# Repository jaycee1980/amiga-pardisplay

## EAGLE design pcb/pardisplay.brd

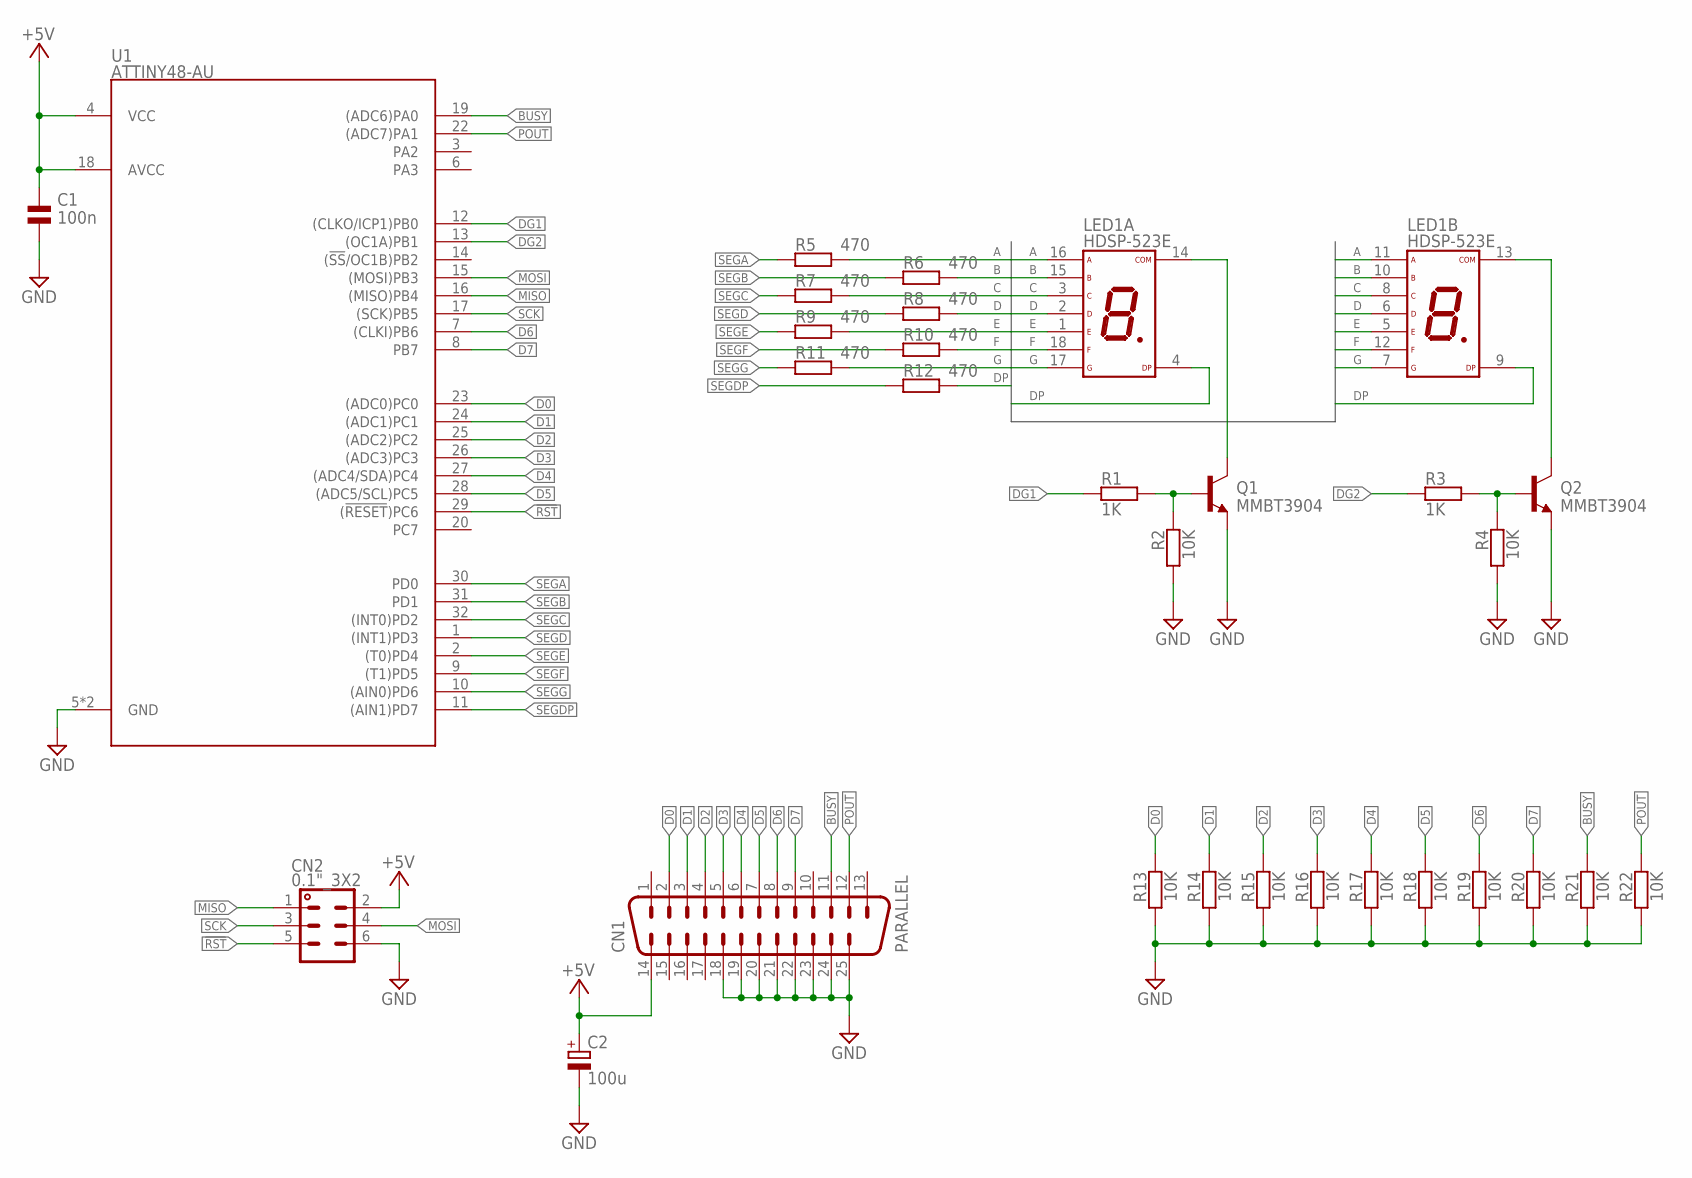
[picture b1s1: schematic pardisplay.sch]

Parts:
C1: 100n; 0603
C2: 100u; UD-6,3X5,8_NICHICON
CN1: PARALLEL; M25HP
CN2: 0.1"_3X2; 0.1"_3X2-LONG
LED1: HDSP-523E; DA56
Q1, Q2: MMBT3904; SOT23
R1, R3: 1K; 0603
R2, R4, R13, R14, R15, R16, R17, R18, R19, R20, R21, R22: 10K; 0603
R5, R6, R7, R8, R9, R10, R11, R12: 470; 0603
U1: ATTINY48-AU; TQFP32-08

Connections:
!RST: CN2.5, U1.29 ((!RESET!)PC6)
+5V: C1.1, C2.+, CN1.14, CN2.2, U1.4 (VCC), U1.18 (AVCC)
A: LED1.11 (A), LED1.16 (A), R5.2
B: LED1.10 (B), LED1.15 (B), R6.2
BUSY: CN1.11, R21.1, U1.19 ((ADC6)PA0)
C: LED1.3 (C), LED1.8 (C), R7.2
COM1: LED1.14 (COM), Q1.3 (C)
COM2: LED1.13 (COM), Q2.3 (C)
D: LED1.2 (D), LED1.6 (D), R8.2
D0: CN1.2, R13.1, U1.23 ((ADC0)PC0)
D1: CN1.3, R14.1, U1.24 ((ADC1)PC1)
D2: CN1.4, R15.1, U1.25 ((ADC2)PC2)
D3: CN1.5, R16.1, U1.26 ((ADC3)PC3)
D4: CN1.6, R17.1, U1.27 ((ADC4/SDA)PC4)
D5: CN1.7, R18.1, U1.28 ((ADC5/SCL)PC5)
D6: CN1.8, R19.1, U1.7 ((CLKI)PB6)
D7: CN1.9, R20.1, U1.8 (PB7)
DG1: R1.1, U1.12 ((CLKO/ICP1)PB0)
DG2: R3.1, U1.13 ((OC1A)PB1)
DP: LED1.4 (DP), LED1.9 (DP), R12.2
E: LED1.1 (E), LED1.5 (E), R9.2
F: LED1.12 (F), LED1.18 (F), R10.2
G: LED1.7 (G), LED1.17 (G), R11.2
GND: C1.2, C2.-, CN1.18, CN1.19, CN1.20, CN1.21, CN1.22, CN1.23, CN1.24, CN1.25, CN2.6, Q1.2 (E), Q2.2 (E), R2.2, R4.2, R13.2, R14.2, R15.2, R16.2, R17.2, R18.2, R19.2, R20.2, R21.2, R22.2, U1.5 (GND), U1.21 (GND)
MISO: CN2.1, U1.16 ((MISO)PB4)
MOSI: CN2.4, U1.15 ((MOSI)PB3)
unnamed: Q1.1 (B), R1.2, R2.1
unnamed: Q2.1 (B), R3.2, R4.1
POUT: CN1.12, R22.1, U1.22 ((ADC7)PA1)
SCK: CN2.3, U1.17 ((SCK)PB5)
SEGA: R5.1, U1.30 (PD0)
SEGB: R6.1, U1.31 (PD1)
SEGC: R7.1, U1.32 ((INT0)PD2)
SEGD: R8.1, U1.1 ((INT1)PD3)
SEGDP: R12.1, U1.11 ((AIN1)PD7)
SEGE: R9.1, U1.2 ((T0)PD4)
SEGF: R10.1, U1.9 ((T1)PD5)
SEGG: R11.1, U1.10 ((AIN0)PD6)

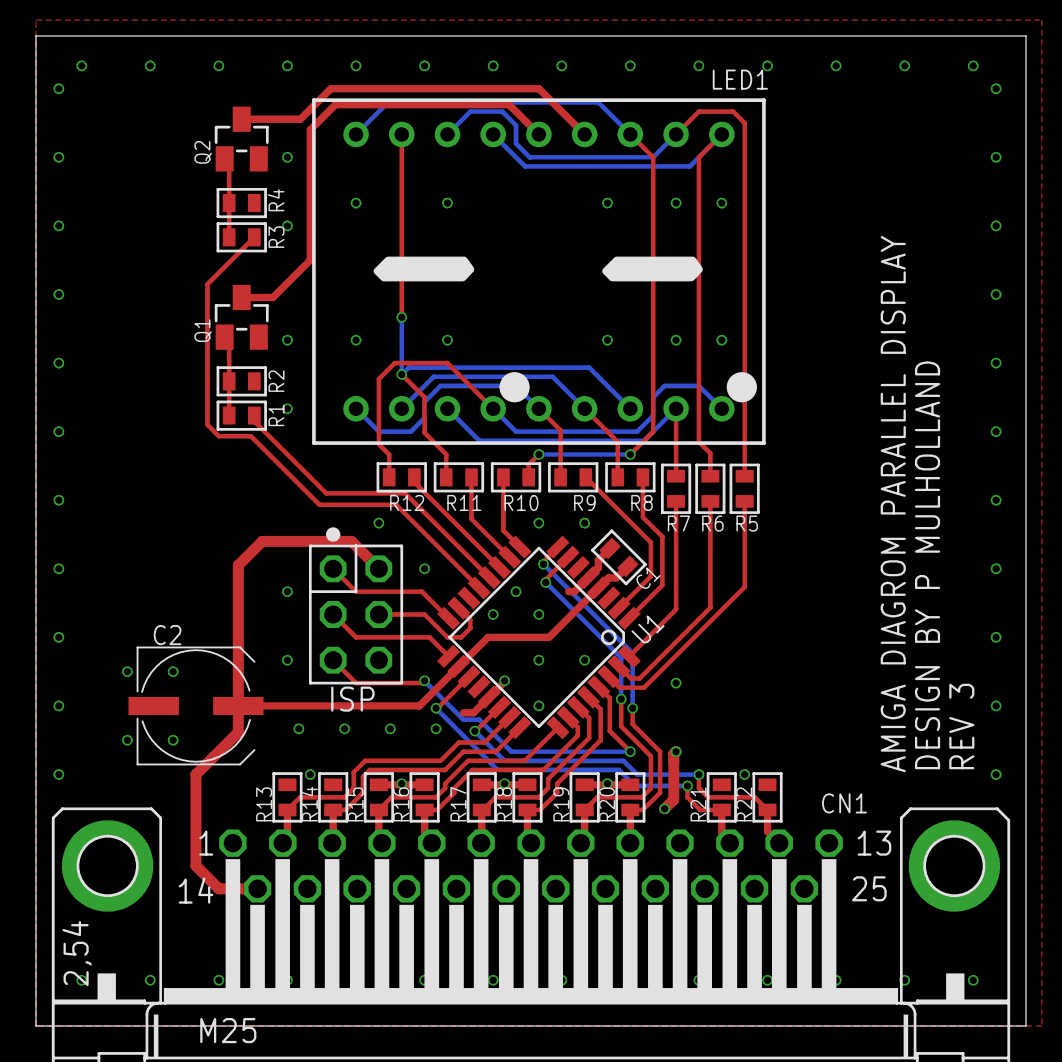
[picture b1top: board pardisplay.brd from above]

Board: 2 copper layers, 55.0 x 55.0 mm, 30 parts (0 on the bottom side), 38 nets.

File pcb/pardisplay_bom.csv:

Comment,Designator,Footprint,LCSC Part #
1K,R1 R3,0603,C21190
10K,R2 R4 R13 R14 R15 R16 R17 R18 R19 R20 R21 R22,0603,C25804
470R,R5 R6 R7 R8 R9 R10 R11 R12,0603,C23179
100nF,C1,0603,C14663
100uF,C2,D6.3xL5.4mm,C340722
ATtiny88-AU,U1,TQFP32,C111451
MMBT3904,Q1 Q2,SOT-23,C20526

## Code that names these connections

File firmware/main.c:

/*******************************************************************************************************************//**
	DiagROM Parallel Port display
	\author Peter Mulholland
***********************************************************************************************************************/

#include <stdint.h>
#include <avr/io.h>
#include <avr/wdt.h>
#include <avr/pgmspace.h>
#include <avr/cpufunc.h>
#include <avr/sleep.h>
#include <avr/interrupt.h>

//----------------------------------------------------------------------------------------------------------------------
/*
	ATtiny48/88

	lfuse 0x6E - internal 8MHz oscillator, divided to 1MHz
	hfuse 0xDF - brownout detection disabled, SPI programming enabled

	PA0		input, BUSY pin of parallel port
	PA1		input, PAPER OUT pin of parallel port

	PB0		output, digit 1 enable
	PB1		output, digit 2 enable
	PB6-7	input, parallel port D6-D7

	PC0-5	input, parallel port D0-D5

	PD0-7	output, segment anodes

*/

//#define _DEBUG

//----------------------------------------------------------------------------------------------------------------------
// PROGMEM data

// Digit segment definitions, 1 = segment ON
const uint8_t c_digits[] PROGMEM = {
//    .GFEDCBA
	0b00111111,		// 0
	0b00000110,		// 1
	0b01011011,		// 2
	0b01001111,		// 3
	0b01100110,		// 4
	0b01101101,		// 5
	0b01111101,		// 6
	0b00000111,		// 7
	0b01111111,		// 8
	0b01101111,		// 9
	0b01110111,		// A
	0b01111100,		// b
	0b01011000,		// c
	0b01011110,		// d
	0b01111001,		// E
	0b01110001		// F
};

//----------------------------------------------------------------------------------------------------------------------
// ISRs

ISR(TIMER0_OVF_vect)
{
#ifdef _DEBUG
	// Make a pulse on our debugging pin
	PINB = _BV(PINB5);
	_NOP();
	PINB = _BV(PINB5);
#endif

	// Cause an immediate overflow to make our interrupts occur with no further division
	TCNT0 = 255;
}

//----------------------------------------------------------------------------------------------------------------------
// Main

int main(void)
{
	uint8_t state = 0;		// Current digit being displayed
	uint8_t val = 0;		// The value last read from the parallel port

	// Disable the watchdog timer
	wdt_disable();

	// We're only using Timer 0 - turn the rest off
	PRR = _BV(PRTWI) | _BV(PRTIM1) | _BV(PRSPI) | _BV(PRADC);

	// Set port A so all pins are inputs. Set pullups on unused inputs PA2 and PA3
	PORTA = _BV(PORTA2) | _BV(PORTA3);
	DDRA  = 0;

#ifndef _DEBUG
	// Set port B so PB0 and PB1 are outputs, all others are inputs.
	// PB0-1 should be low, PB6-PB7 have no pullups
	PORTB = _BV(PORTB2) | _BV(PORTB3) | _BV(PORTB4) | _BV(PORTB5);
	DDRB  = _BV(DDB0) | _BV(DDB1);
#else
	// Make PB5 (the SCK pin) an output for debugging the interrupt speed
	PORTB = _BV(PORTB2) | _BV(PORTB3) | _BV(PORTB4);
	DDRB = _BV(DDB0) | _BV(DDB1) | _BV(DDB5);
#endif

	// Set port C so PC0-5 are inputs with no pullups
	PORTC = _BV(PORTC6) | _BV(PORTC7);
	DDRC  = 0;

	// Set port D to all outputs, initially low
	PORTD = 0;
	DDRD  = 0xFF;

	// Wait for port states to synchronise
	_NOP(); _NOP();

	// Set up Timer 0 interrupt so we wake up at regular intervals
	TIFR0 = 0;								// Clear timer flags
	TCNT0 = 255;							// Immediate overflow
	TIMSK0 = _BV(TOIE0);					// Timer overflow interrupt on
	TCCR0A = (_BV(CS01) | _BV(CS00));		// 1MHz / 64 = 15.625KHz

	// Set sleep mode to Idle so that the Timer0 overflow interrupt can wake us up
	set_sleep_mode(SLEEP_MODE_IDLE);

	// Interrupts on!
	sei();

	// Loop
	for (;;)
	{
		uint8_t digit = 0;

		// Turn off both digits
		PORTB &= ~(_BV(PORTB0) | _BV(PORTB1));

		if (state == 0)
		{
			// read the parallel port value
			val = (PINB & 0xC0) | (PINC & 0x3F);

			// Display first digit
			digit = pgm_read_byte(&c_digits[val >> 4]);

			if (PINA & _BV(PINA0))			// if BUSY pin of parallel port is high
				digit |= 0x80;				// Turn on the decimal point

			PORTD = digit;
			PORTB |= _BV(PORTB0);
		}
		else
		{
			// Display second digit
			digit = pgm_read_byte(&c_digits[val & 0x0F]);

			if (PINA & _BV(PINA1))			// if POUT pin of parallel port is high
				digit |= 0x80;				// Turn on the decimal point

			PORTD = digit;
			PORTB |= _BV(PORTB1);
		}

		// Toggle digit to show
		state = !state;

		// Until the next interrupt
		sleep_enable();
		sleep_cpu();
	}
	
	// We never get here!
	return 0;
}

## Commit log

2025-05-04 Create LICENSE
